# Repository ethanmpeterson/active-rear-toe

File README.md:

# active-rear-toe
Arduino Code that controls Rear wheel steering on Queen's Formula

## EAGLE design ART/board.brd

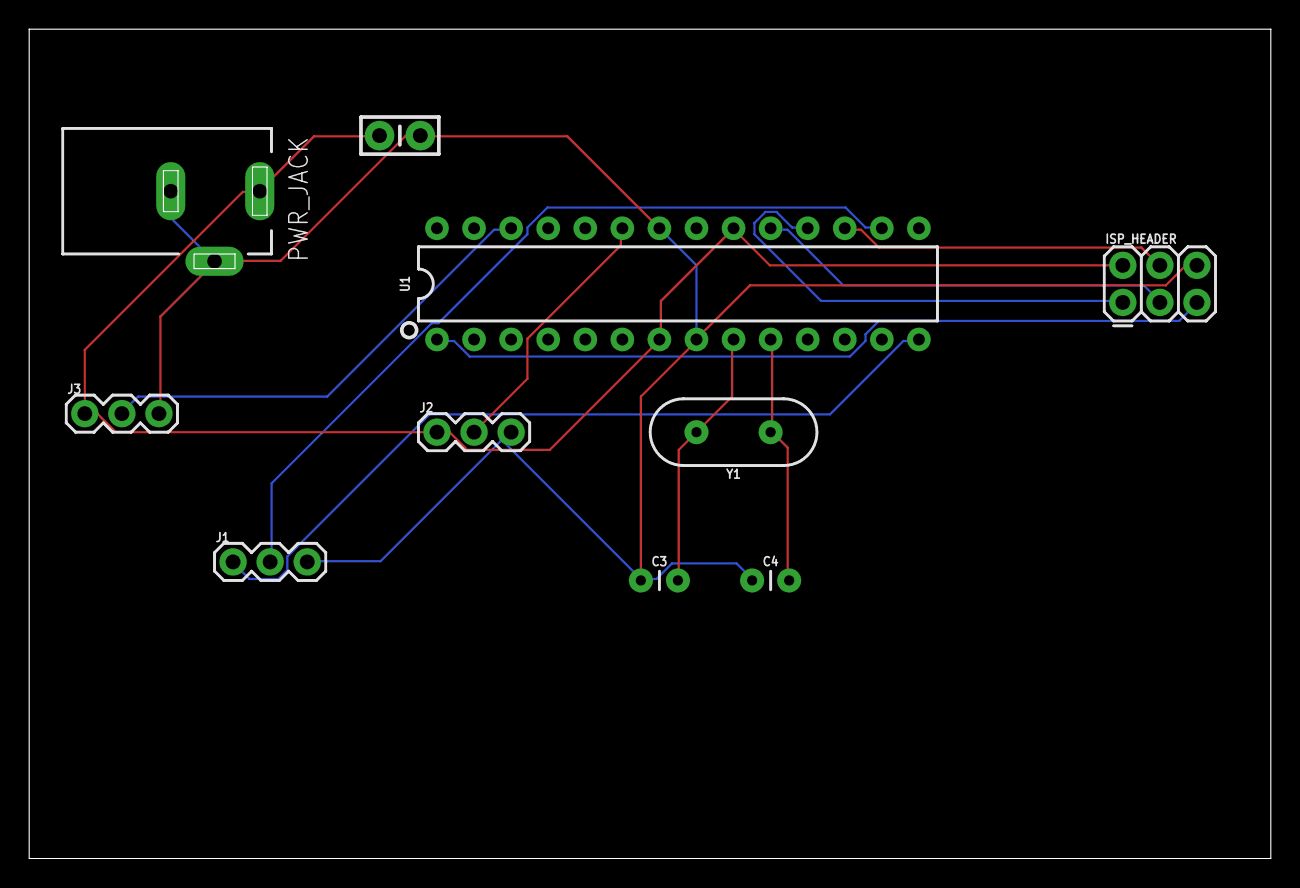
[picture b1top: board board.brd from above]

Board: 2 copper layers, 85.1 x 56.8 mm, 10 parts (0 on the bottom side), 12 nets.

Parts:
C1: 0.1uF; CAP-PTH-SMALL-KIT
C3, C4: 22pF; CAP-PTH-2.54
ISP_HEADER: FEMALE 2x3; 2X3
J1, J2, J3: 455-1750-1-ND; 1X03
PWR_JACK: DCJ0202
U1: 328P; DIP28
Y1: 16MHz; HC49US

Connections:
DIRN: J1.1, U1.14
GND: C1.2, C3.1, C4.1, ISP_HEADER.6, J1.3, J2.3, J3.3, PWR_JACK.2, PWR_JACK.3, U1.8, U1.22
MISO: ISP_HEADER.1, U1.18
MOSI: ISP_HEADER.4, U1.17
unnamed: C3.2, U1.9, Y1.2
unnamed: C4.2, U1.10, Y1.1
POS: J2.2, U1.23
PWM: J1.2, U1.16
RESET: ISP_HEADER.5, U1.1
SCK: ISP_HEADER.3, U1.19
STEER: J3.2, U1.26
VCC: C1.1, ISP_HEADER.2, J2.1, J3.1, PWR_JACK.1, U1.7, U1.20

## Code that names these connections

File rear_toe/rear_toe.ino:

#include <EEPROM.h> // to record steering input data and measure against position where the motor should be

// AVR Libs for Timer Interrupts
#include <avr/io.h>
#include <avr/interrupt.h>

#define POT_VCC A5
#define POT_GND A1

// CAR SENSOR INPUT PINS
#define POS_PIN A0 // mapped to wiper pin of potentiometer reporting actuator position
#define STEER_PIN A3 // voltage between 0.5 - 4.5V
#define BRAKE_PIN 12

#define DIRN 8
#define PWM 10


// since steering input is given from 0.5V to 4.5V we must set bounds and constrain
#define UPPER 921 // approx 4.5V from ADC reading
#define LOWER 102 // approx 0.5V ADC reading

#define BAUD 9600

// LIMIT ACTUATOR READINGS (MAX POSITION OF ACTUATOR IN EITHER DIRN)
#define AC_UPPER 964
#define AC_LOWER 927

// POSITION MAXIMUMS of +- 3 degrees as per league regulations
#define REG_UPPER 960
#define REG_LOWER 945 

#define CENTER 955 // when wheels are straight
#define DUTY 255 // DUTY cycle for the PWM PIN controlling the actuator set to 60 to move it slowly to prevent breaking anything
#define TOLERANCE 1 // error in the actuator reading that will be excepted ex pos should be 935 stop at reading of 936 if tolerance is 1

#define TOTAL_ENTRIES 170 // total number of EEPROM entries before running out of memory
/*
  DRIVE_MODE
  0 : Accel Mode (Wheels stay straight)
  1 : Skid Pad (Wheels Turn Opposite to steering input)
  2 : Autocross / Endurance (Speed Influences Wheel behaviour)
*/
#define DRIVE_MODE 1

int reading = 0;
volatile int steerIn = 0;

int addr = 0; // starting EEPROM write address.
struct dataStore {
  int steerPos;
  int actuatorPos; // actual position of actuator
  int intendedPos; // where actuator should be for that steering value
}; // will use this data to measure the amount of error in the system.
// a potentiometer will act as a steering wheel.

void timerInit() {
  cli(); // disable interrupts to do config
  TCCR1A = 0;
  TCCR1B = 0; // Set timer counter registers to 0
  
  TIMSK1 = (1 << TOIE1); // Enable the timer overflow interrupt
  TCCR1B |= (1 << CS10); // set CS10 bit meaning timer will tick at clock speed meaning overflow after 65535 clock cycles

  sei();
}

void setup() {
  //timerInit();
  //cli();
  // put your setup code here, to run once:
  pinMode(DIRN, OUTPUT);
  pinMode(PWM, OUTPUT);
  //analogWrite(PWM, 60);
  // Set up steering pot
  pinMode(A5, OUTPUT);
  pinMode(A1, OUTPUT);
  digitalWrite(POT_VCC, HIGH);
  digitalWrite(POT_GND, LOW);
  // set up actuator position reporting:
  Serial.begin(BAUD);
  Serial.println(sizeof(dataStore));
  setAccelPos(); // re orient to center
}

volatile int actPos = 0;

// ISR
ISR(TIMER1_OVF_vect) {
  if (!approx(reading, actPos, TOLERANCE)) {
    if (reading < actPos) {
      digitalWrite(DIRN, HIGH);
    } else {
      digitalWrite(DIRN, LOW);
    }
    analogWrite(PWM, 60);
    reading = analogRead(POS_PIN);
    Serial.println(reading);
  } else {
    //analogWrite(PWM, 0);
  }
}

int count = 0;
void loop() {
  // put your main code here, to run repeatedly:
  //setAccelMode();

  // Collect Data
  if (count < TOTAL_ENTRIES) {
    dataStore store = {
      steerIn,
      analogRead(POS_PIN),
      actPos
    };
    EEPROM.put(addr, store);
    addr += sizeof(dataStore);
    count++;
  } else {
    Serial.println("DATA RECORD COMPLETE");
  }
  
  reading = analogRead(POS_PIN);
  steerIn = constrain(analogRead(STEER_PIN), LOWER, UPPER);
  uint8_t brakes = digitalRead(BRAKE_PIN);

  // Update Rear Wheels
  if (DRIVE_MODE == 0) {
    setPos(CENTER);
  } else if (DRIVE_MODE == 1) {
    actPos = map(steerIn, LOWER, UPPER, REG_LOWER, REG_UPPER);
    setPos(actPos);
  }
  
  // record actuator position
  //Serial.print("ACTUATOR: ");
  //Serial.println(analogRead(POS_PIN));
}

void setAccelPos() {
  while (!approx(reading, CENTER, TOLERANCE)) {
    if (reading < CENTER) {
      digitalWrite(DIRN, HIGH);
    } else {
      digitalWrite(DIRN, LOW);
    }
    analogWrite(PWM, 60);
    reading = analogRead(POS_PIN);
    //Serial.println(reading);
  }
  analogWrite(PWM, 0);
}

void setPos(int pos) { // general function called in a loop to set actuator to desired position
    while (!approx(reading, pos, TOLERANCE)) {
    if (reading < pos) {
      digitalWrite(DIRN, HIGH);
    } else {
      digitalWrite(DIRN, LOW);
    }
    analogWrite(PWM, 60);
    reading = analogRead(POS_PIN);
    Serial.println(reading);
  }
  analogWrite(PWM, 0);
}

uint8_t approx(int val, int target, int error) { // returns true if val is within the error range
  return abs(val - target) <= error;
}

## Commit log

2018-11-26 initial code commit plus accel mode and set pos functions
2018-11-26 added approx equal function
2018-11-26 tested approx func
2019-01-11 began work with potentiometer test steering input
2019-01-11 code cleanup and update to maximum position values
2019-01-11 mapped pot input to wheel turn. wheel position range still needs adjustment
2019-01-11 added data collection which will collect test data from EEPROM
2019-01-11 wrote test data to EEPROM and completed data collection sketch
2019-01-11 added text file carrying first set of results
2019-01-11 started python script script to parse and analyze data in the text file
2019-01-12 set up line parsing function
2019-01-12 set up dictionary data format
2019-01-12 calculated average difference still need to convert to % #1
2019-01-13 started on csv output so data can be looked at in excel
2019-01-14 fixed error with csv write will also add json
2019-01-14 added the completed fritzing and diagram and started on eagle schematic
2019-01-19 added board and schematic renders
2019-01-24 fixed #3
2019-02-09 timer inturrupt code

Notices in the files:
parts and their libraries:
SparkFun-Capacitors: Licensing: Creative Commons ShareAlike 4.0 International - https://creativecommons.org/licenses/by-sa/4.0
